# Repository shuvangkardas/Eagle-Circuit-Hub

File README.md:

# Eagle Circuit Hub

<!-- Badges -->
[![GitHub release][release-shield]][release-url]
[![GitHub commits][commits-shield]][commits-url]
[![MIT License][license-shield]][license-url]

## Commonly used Schematic for building circuit board

This is a collection of my schematic for developing designing PCB board in Eagle PCB in a short time. The library contains follwing sub-directory. 
- Microcontroller 
- Power Supply 
- RF
- RF SOC
- Timer
- Sensor
- Switch 
- Connectors
- Memory

### Microcontroller
- ATmega328P.sch
- ATmega328P_SMD_0603.sch
- MSP430FR2433_SMD_0603.sch

### Power Supply 
- LM2596.sch
- LM2596_SMD_0603.sch
- 1117_3.3V.sch
- 1117_3.3V_SMD_0603.sch
- 1117_Adj.sch
- 1117_Adj_SMD_0603.sch
- 7805.sch
- 7805_SMD_0603.sch
- LM2596.sch
- LM2596_SMD_0603.sch
- TPS6273x.sch

## Common SMD Components used
1. Resistor - R-US_R0603
2. Capacitor - C-EUC0603
3. Inductor - L-USL0603 

<!-- MARKDOWN LINKS & IMAGES -->
[release-shield]: https://img.shields.io/github/v/release/shuvangkar/Eagle-Circuit-Hub
[release-url]: https://img.shields.io/github/v/release/shuvangkar/Eagle-Circuit-Hub

[commits-shield]: https://img.shields.io/github/commits-since/shuvangkar/Eagle-Circuit-Hub/v0.1.0
[commits-url]: https://github.com/shuvangkar/Eagle-Circuit-Hub/commits/master

[license-shield]: https://img.shields.io/github/license/shuvangkar/Eagle-Circuit-Hub
[license-url]: https://github.com/shuvangkar/Eagle-Circuit-Hub/blob/master/LICENSE.txt

[linkedin-shield]: https://img.shields.io/badge/-LinkedIn-black.svg?logo=linkedin&colorB=555
[linkedin-url]: https://linkedin.com/in/shuvangkar

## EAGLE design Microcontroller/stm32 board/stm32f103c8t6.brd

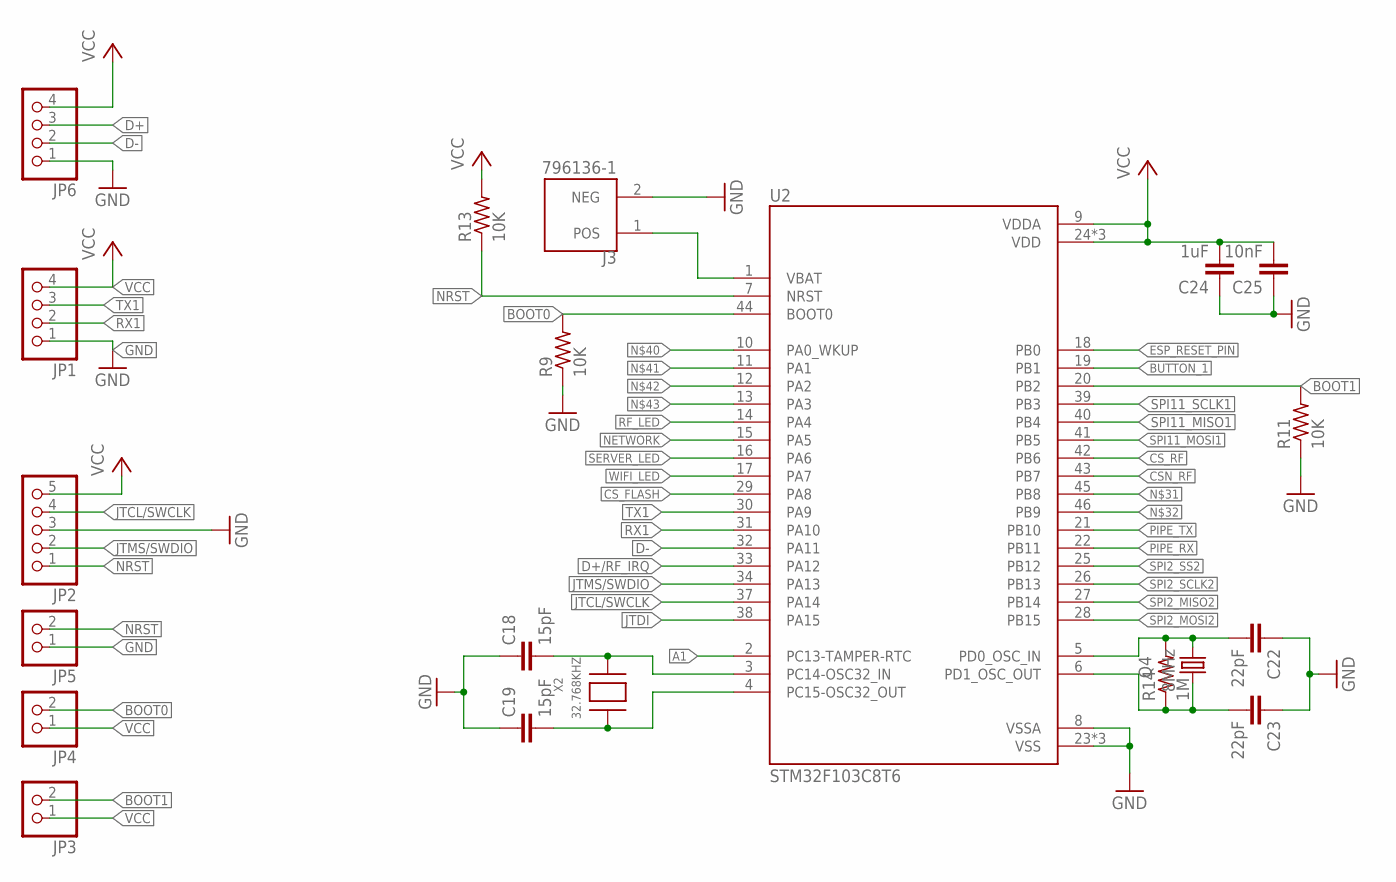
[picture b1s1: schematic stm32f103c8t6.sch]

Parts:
C18, C19: 15pF; C0603
C22, C23: 22pF; C0603
C24: 1uF; C0603
C25: 10nF; C0603
J3: 796136-1; TE_796136-1
JP1, JP6: PINHD-1X4; 1X04
JP2: PINHD-1X5; 1X05
JP3, JP4, JP5: PINHD-1X2; 1X02
Q4: 8MHz; 3.2X2.5_KX-7
R9, R11, R13: 10K; R0603
R14: 1M; R0603
U2: STM32F103C8T6; QFP50P900X900X160-48N
X2: 32.768KHZ; XTAL3215

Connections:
A1: U2.2 (PC13-TAMPER-RTC)
BOOT0: JP4.2, R9.2, U2.44 (BOOT0)
BOOT1: JP3.2, R11.2, U2.20 (PB2)
BUTTON_1: U2.19 (PB1)
CSN_RF: U2.43 (PB7)
CS_FLASH: U2.29 (PA8)
CS_RF: U2.42 (PB6)
D+: JP6.3
D+/RF_IRQ: U2.33 (PA12)
D-: JP6.2, U2.32 (PA11)
ESP_RESET_PIN: U2.18 (PB0)
GND: C18.1, C19.1, C22.1, C23.1, C24.1, C25.1, J3.2 (NEG), JP1.1, JP2.3, JP5.1, JP6.1, R9.1, R11.1, U2.8 (VSSA), U2.23 (VSS), U2.35 (VSS), U2.47 (VSS)
JTCL/SWCLK: JP2.4, U2.37 (PA14)
JTDI: U2.38 (PA15)
JTMS/SWDIO: JP2.2, U2.34 (PA13)
unnamed: C18.2, U2.3 (PC14-OSC32_IN), X2.P$2
unnamed: C19.2, U2.4 (PC15-OSC32_OUT), X2.P$1
unnamed: C23.2, Q4.3 (2), R14.1, U2.6 (PD1_OSC_OUT)
unnamed: C22.2, Q4.1, R14.2, U2.5 (PD0_OSC_IN), U2.45 (PB8)
unnamed: J3.1 (POS), U2.1 (VBAT), U2.46 (PB9)
NETWORK: U2.15 (PA5)
NRST: JP2.1, JP5.2, R13.1, U2.7 (NRST)
PIPE_RX: U2.22 (PB11)
PIPE_TX: U2.21 (PB10)
RF_LED: U2.14 (PA4)
RX1: JP1.2, U2.31 (PA10)
SERVER_LED: U2.16 (PA6)
SPI2_MISO2: U2.27 (PB14)
SPI2_MOSI2: U2.28 (PB15)
SPI2_SCLK2: U2.26 (PB13)
SPI2_SS2: U2.25 (PB12)
SPI11_MISO1: U2.40 (PB4)
SPI11_MOSI1: U2.41 (PB5)
SPI11_SCLK1: U2.39 (PB3)
TX1: JP1.3, U2.30 (PA9)
VCC: C24.2, C25.2, JP1.4, JP2.5, JP3.1, JP4.1, JP6.4, R13.2, U2.9 (VDDA), U2.24 (VDD), U2.36 (VDD), U2.48 (VDD)
WIFI_LED: U2.17 (PA7)

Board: 2 copper layers, 20 parts (0 on the bottom side), 15 nets, no tracks yet.

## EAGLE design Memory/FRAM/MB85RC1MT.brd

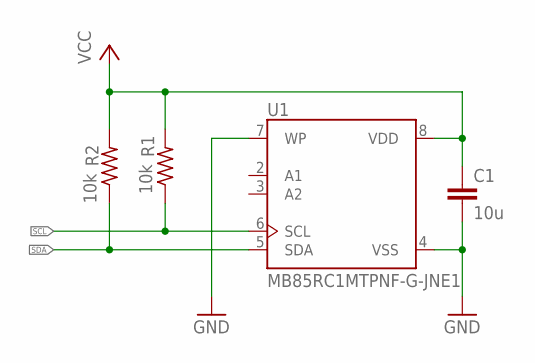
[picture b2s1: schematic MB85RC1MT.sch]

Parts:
C1: 10u; C0603
R1, R2: 10k; R0603
U1: MB85RC1MTPNF-G-JNE1; SOIC127P620X175-8N

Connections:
GND: C1.2, U1.4 (VSS), U1.7 (WP)
SCL: R1.1, U1.6 (SCL)
SDA: R2.1, U1.5 (SDA)
VCC: C1.1, R1.2, R2.2, U1.8 (VDD)

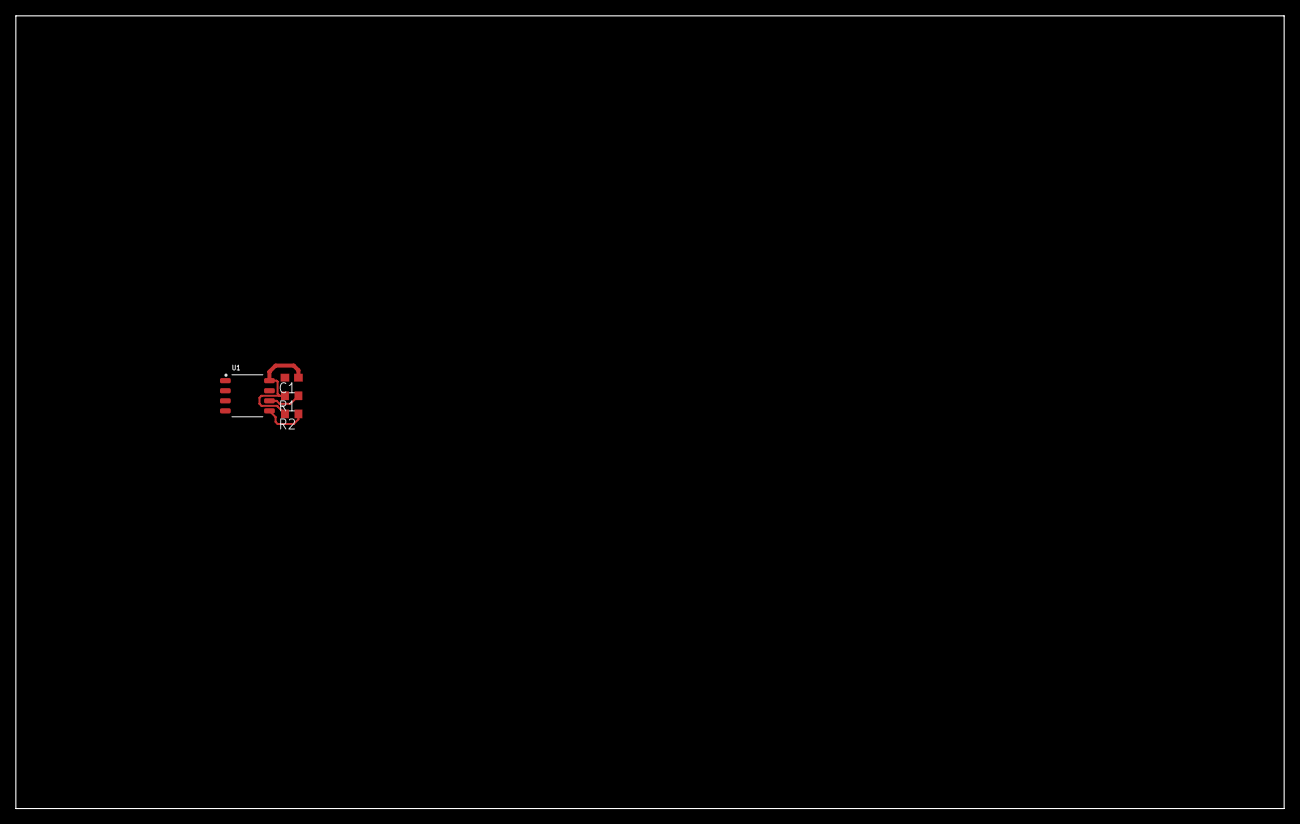
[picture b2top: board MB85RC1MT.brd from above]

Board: 2 copper layers, 160.0 x 100.0 mm, 4 parts (0 on the bottom side), 4 nets.

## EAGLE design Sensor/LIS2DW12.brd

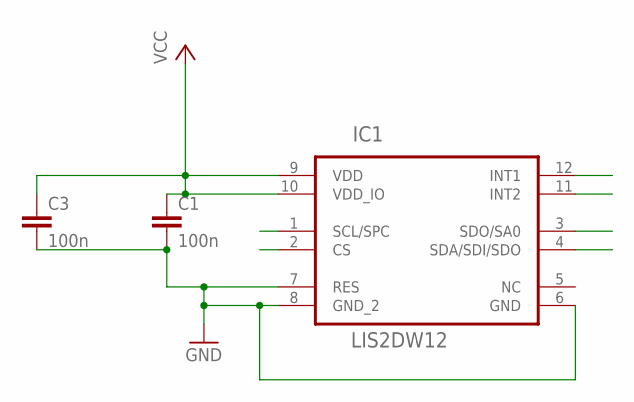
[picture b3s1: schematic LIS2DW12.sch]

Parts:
C1, C3: 100n; C0402
IC1: LIS2DW12; LGA-12

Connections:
GND: C1.2, C3.2, IC1.6 (GND), IC1.7 (RES), IC1.8 (GND_2)
VCC: C1.1, C3.1, IC1.9 (VDD), IC1.10 (VDD_IO)

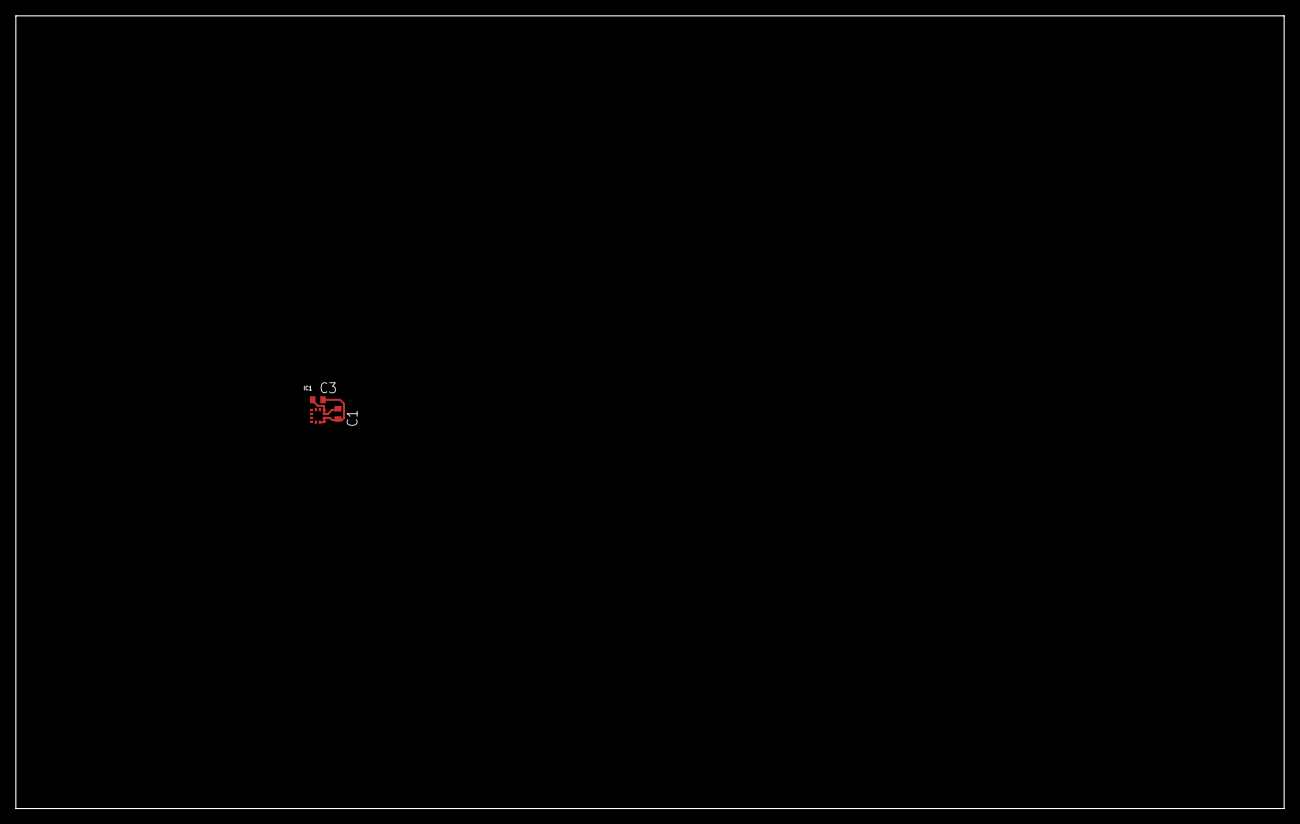
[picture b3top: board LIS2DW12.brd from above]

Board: 2 copper layers, 160.0 x 100.0 mm, 3 parts (0 on the bottom side), 2 nets.

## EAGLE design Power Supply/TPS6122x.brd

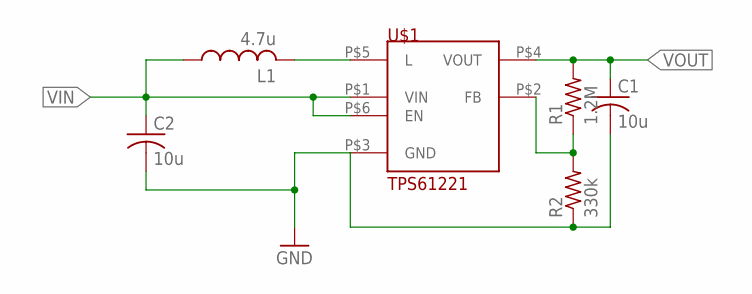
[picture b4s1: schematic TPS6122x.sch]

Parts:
C1, C2: 10u; C3216
L1: 4.7u; L1210
R1: 1.2M; R0603
R2: 330k; R0603
U$1: TPS61221

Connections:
GND: C1.2, C2.2, R2.1, U$1.P$3 (GND)
unnamed: L1.2, U$1.P$5 (L)
unnamed: R1.1, R2.2, U$1.P$2 (FB)
VIN: C2.1, L1.1, U$1.P$1 (VIN), U$1.P$6 (EN)
VOUT: C1.1, R1.2, U$1.P$4 (VOUT)

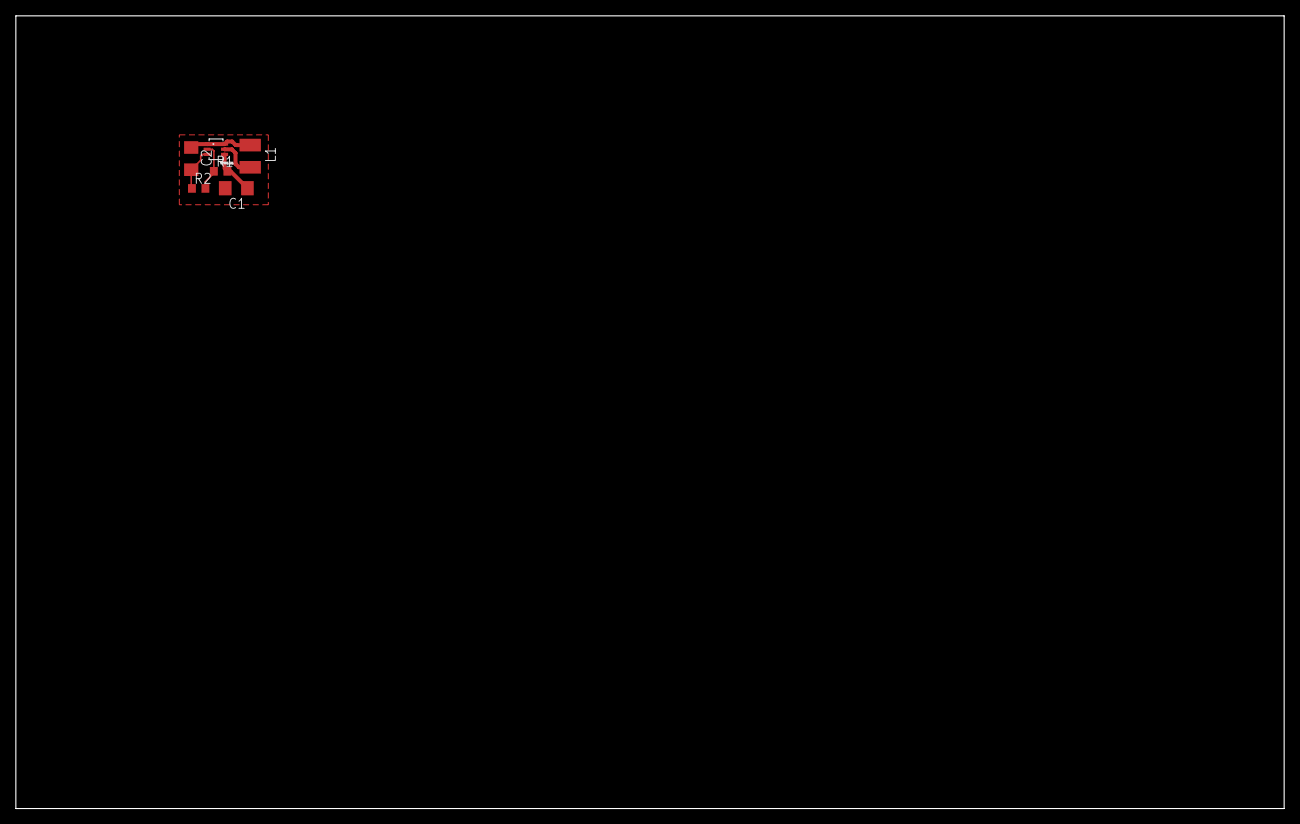
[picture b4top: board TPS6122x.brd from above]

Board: 2 copper layers, 160.0 x 100.0 mm, 6 parts (0 on the bottom side), 5 nets.

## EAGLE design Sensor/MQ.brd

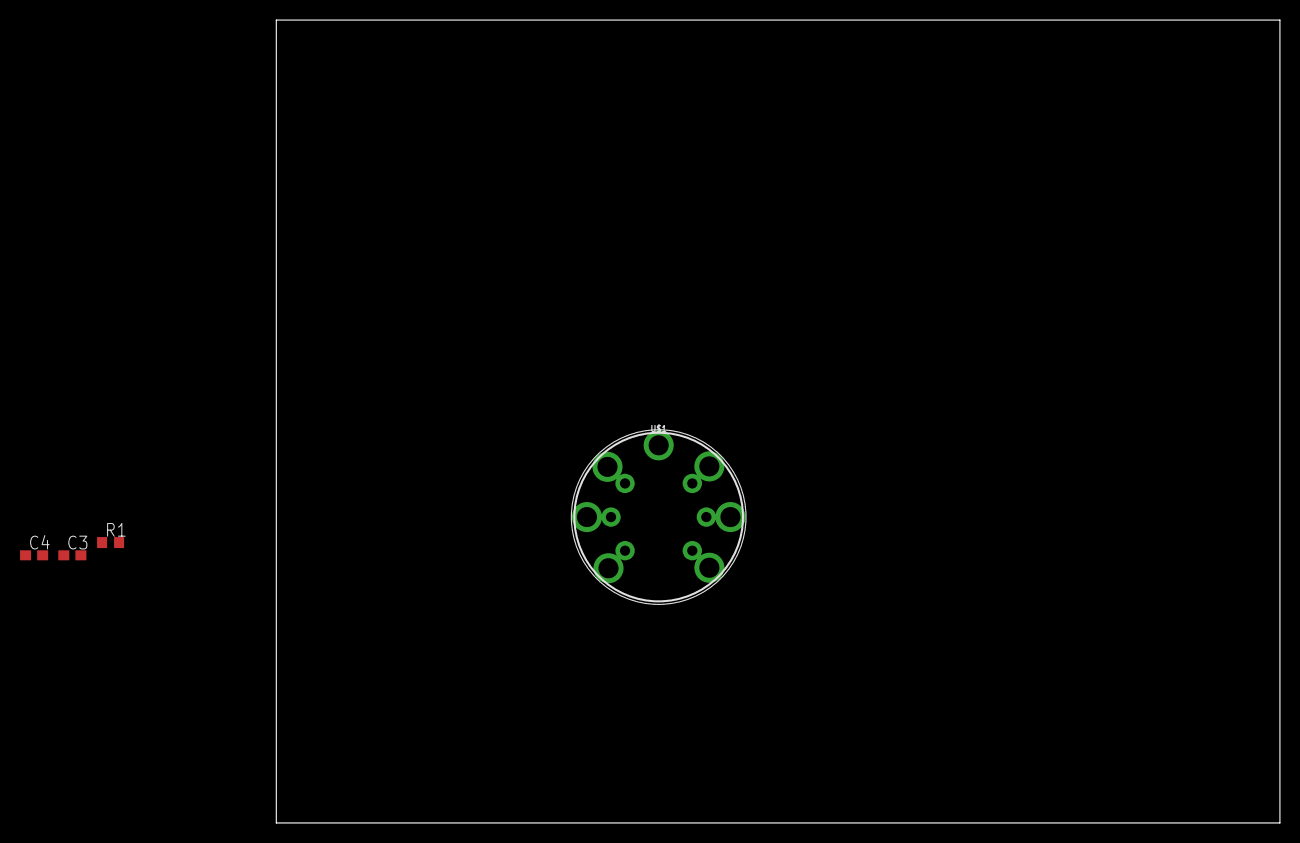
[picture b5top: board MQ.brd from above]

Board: 2 copper layers, 100.0 x 80.0 mm, 4 parts (0 on the bottom side), 3 nets, no tracks yet.

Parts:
C3, C4: C0603
R1: 10k; R0603
U$1: MQ_GAS_SENSOR_SOCKET; GAS_SENSOR_SOCKET

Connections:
GND: C3.2, C4.2, R1.1, U$1.H2, U$1.H22
MQ_OUT: R1.2, U$1.B1, U$1.B2, U$1.B11, U$1.B22
VCC: C3.1, C4.1, U$1.A1, U$1.A2, U$1.A11, U$1.A22, U$1.H1, U$1.H11

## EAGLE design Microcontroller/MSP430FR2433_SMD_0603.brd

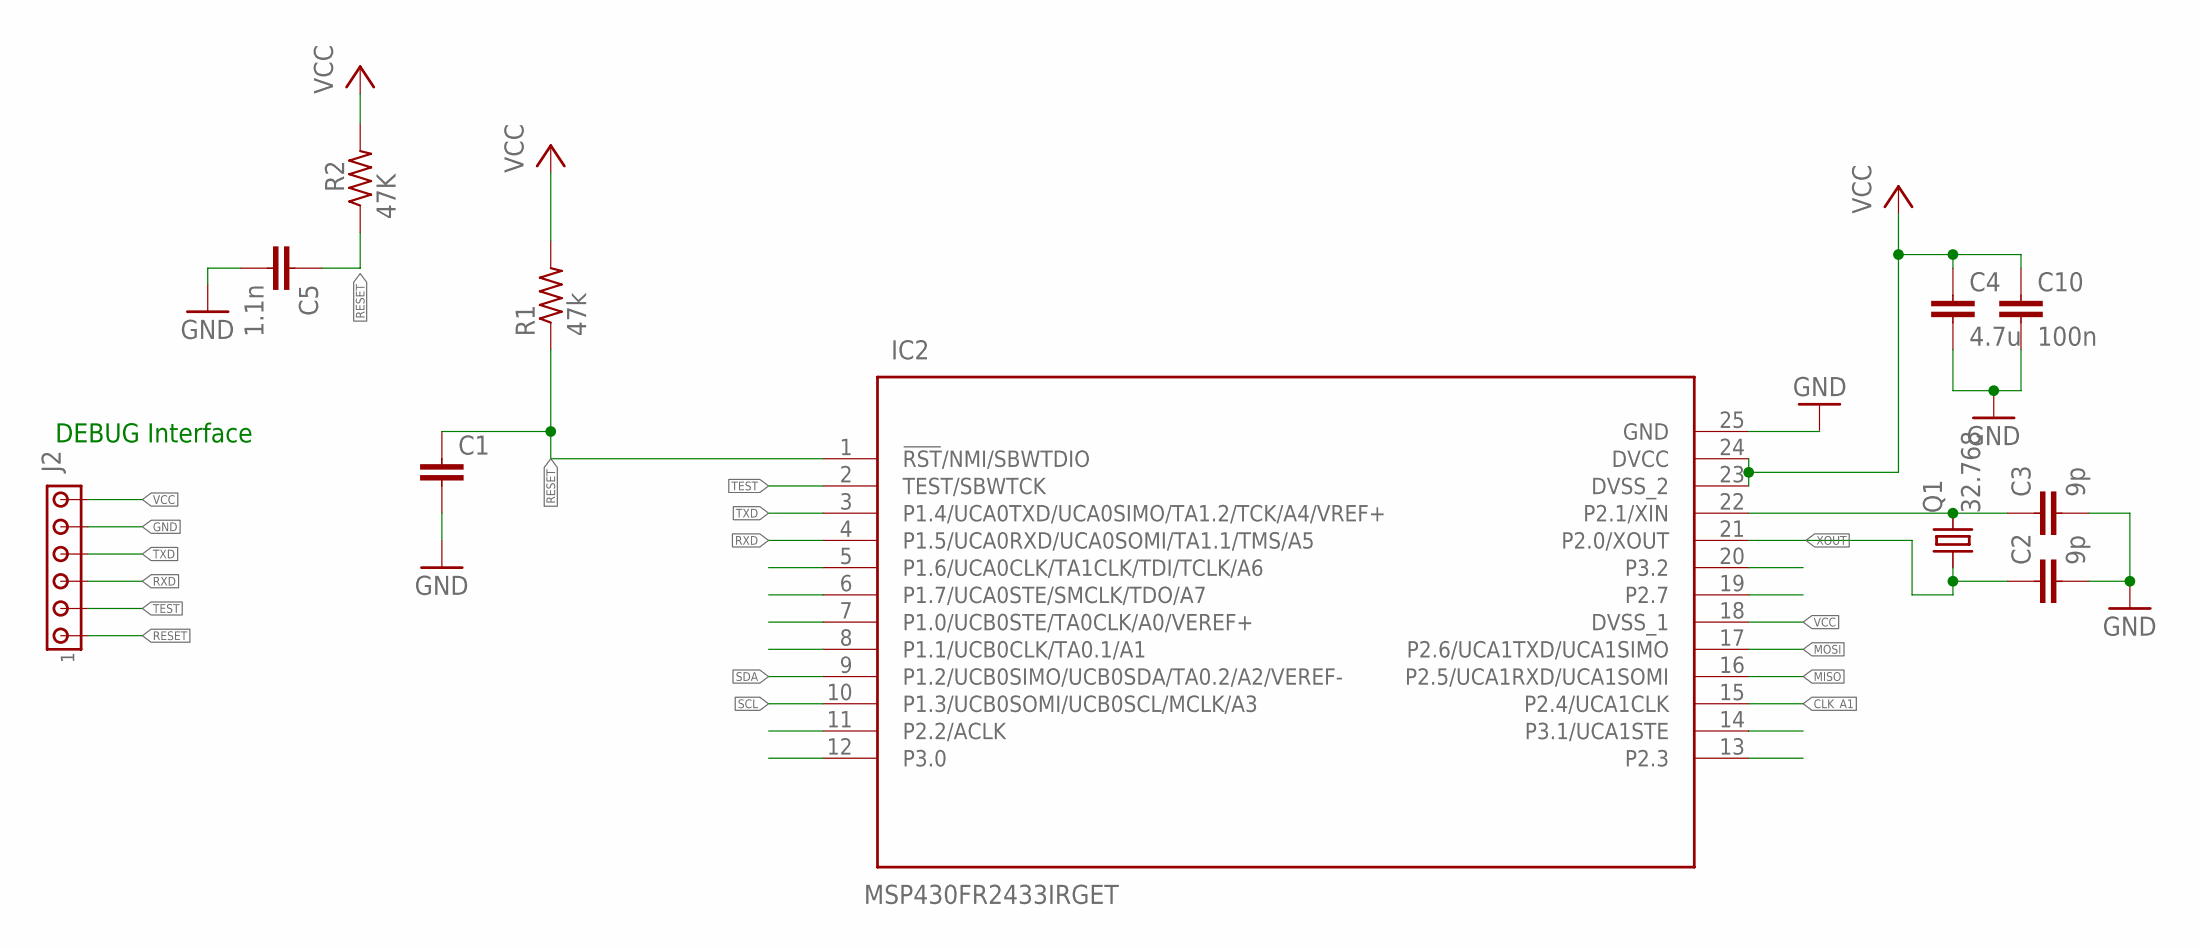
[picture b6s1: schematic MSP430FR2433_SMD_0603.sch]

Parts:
C1: C-EUC0402; C0402
C2, C3: 9p; C0402
C4: 4.7u; C0402
C5: 1.1n; C0402
C10: 100n; C0402
IC2: MSP430FR2433IRGET; QFN50P400X400X100-25N
J2: MTA06-100; 10X06MTA
Q1: 32.768; TC26H
R1: 47k; R0402
R2: 47K; R0402

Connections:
CLK_A1: IC2.15 (P2.4/UCA1CLK)
GND: C1.2, C2.2, C3.2, C4.2, C5.2, C10.2, IC2.25 (GND), J2.5
MISO: IC2.16 (P2.5/UCA1RXD/UCA1SOMI)
MOSI: IC2.17 (P2.6/UCA1TXD/UCA1SIMO)
unnamed: C3.1, IC2.22 (P2.1/XIN), Q1.2
RESET: C1.1, C5.1, IC2.1 (!RST!/NMI/SBWTDIO), J2.1, R1.1, R2.1
RXD: IC2.4 (P1.5/UCA0RXD/UCA0SOMI/TA1.1/TMS/A5), J2.3
SCL: IC2.10 (P1.3/UCB0SOMI/UCB0SCL/MCLK/A3)
SDA: IC2.9 (P1.2/UCB0SIMO/UCB0SDA/TA0.2/A2/VEREF-)
TEST: IC2.2 (TEST/SBWTCK), J2.2
TXD: IC2.3 (P1.4/UCA0TXD/UCA0SIMO/TA1.2/TCK/A4/VREF+), J2.4
VCC: C4.1, C10.1, IC2.18 (DVSS_1), IC2.23 (DVSS_2), IC2.24 (DVCC), J2.6, R1.2, R2.2
XOUT: C2.1, IC2.21 (P2.0/XOUT), Q1.1

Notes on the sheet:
DEBUG Interface

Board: 2 copper layers, 11 parts (0 on the bottom side), 8 nets, no tracks yet.

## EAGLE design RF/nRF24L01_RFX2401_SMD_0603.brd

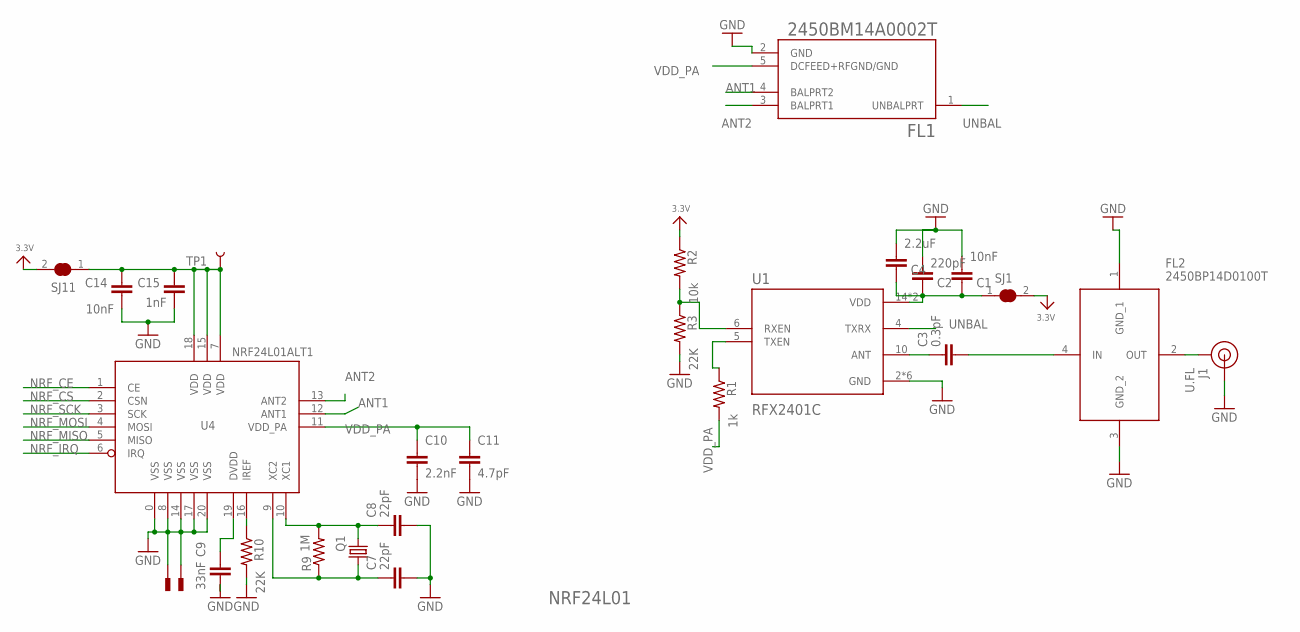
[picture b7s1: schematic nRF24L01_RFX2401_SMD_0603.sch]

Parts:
C1, C14: 10nF; C0603
C2: 220pF; C0603
C3: 0.3pF; C0603
C4: 2.2uF; C0603
C7, C8: 22pF; C0603
C9: 33nF; C0603
C10: 2.2nF; C0603
C11: 4.7pF; C0603
C15: 1nF; C0603
FL1: 2450BM14A0002T; FIL_2450BM14A0002T
FL2: 2450BP14D0100T
J1: U.FL
Q1: KX-7; 3.2X2.5_KX-7
R1: 1k; R0603
R2: 10k; R0603
R3, R10: 22K; R0603
R9: 1M; R0603
SJ1, SJ11: SOLDERJUMPER_CLOSED; SOLDERJUMPER_CLOSEDWIRE
TP1: TEST-POINT3X5; PAD.03X.05
U1: RFX2401C; QFN50P300X300X60-17N
U4: NRF24L01ALT1; QFN20_ALT1
U$27, U$28: PAD; PAD-0.008

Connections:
3.3V: R2.1, SJ1.2, SJ11.2
ANT1: FL1.4 (BALPRT2), U4.12 (ANT1)
ANT2: FL1.3 (BALPRT1), U4.13 (ANT2)
GND: C1.1, C2.1, C4.1, C7.2, C8.2, C9.2, C10.2, C11.2, C14.1, C15.1, FL1.2 (GND), FL2.1 (GND_1), FL2.3 (GND_2), J1.FEED (SIGNAL), R3.2, R10.2, U1.2 (GND), U1.3 (GND), U1.8 (GND), U1.9 (GND), U1.11 (GND), U1.17 (GND), U4.0 (VSS), U4.8 (VSS), U4.14 (VSS), U4.17 (VSS), U4.20 (VSS), U$27.P$1, U$28.P$1
unnamed: C14.2, C15.2, SJ11.1, TP1.P$1, U4.7 (VDD), U4.15 (VDD), U4.18 (VDD)
unnamed: C3.2, FL2.4 (IN)
unnamed: C7.1, Q1.1, R9.1, U4.9 (XC2)
unnamed: FL2.2 (OUT), J1.1 (GND), J1.2 (GND)
unnamed: C3.1, U1.10 (ANT)
unnamed: C1.2, C2.2, C4.2, SJ1.1, U1.14 (VDD), U1.16 (VDD)
unnamed: R1.1, U1.5 (TXEN)
unnamed: C8.1, Q1.3 (2), R9.2, U4.10 (XC1)
unnamed: R2.2, R3.1, U1.6 (RXEN)
unnamed: R10.1, U4.16 (IREF)
unnamed: C9.1, U4.19 (DVDD)
NRF_CE: U4.1 (CE)
NRF_CS: U4.2 (CSN)
NRF_IRQ: U4.6 (IRQ)
NRF_MISO: U4.5 (MISO)
NRF_MOSI: U4.4 (MOSI)
NRF_SCK: U4.3 (SCK)
UNBAL: FL1.1 (UNBALPRT), U1.4 (TXRX)
VDD_PA: C10.1, C11.1, FL1.5 (DCFEED+RFGND/GND), R1.2, U4.11 (VDD_PA)

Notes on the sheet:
NRF24L01

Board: 2 copper layers, 27 parts (0 on the bottom side), 17 nets, no tracks yet.

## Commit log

2020-11-27 Eagle Schematic Library
2020-11-28 gitignore added
2020-11-28 few circuits added
2020-11-28 atmega328 added
2020-11-29 rf, sim , buck circuit added
2020-11-29 flash chip added
2020-11-29 atmega schematic updated
2020-11-29 vcc updated in the circuit
2020-11-29 3.3V regulator added
2020-11-29 led button ckt added
2020-12-01 few ckt updated
2020-12-04 esp12e schematic added
2020-12-07 Rename ATMEGA328PUTQFP_SMD_0603.sch to Microcontroller/ATMEGA328PUTQFP_SMD_0603.sch
2020-12-07 updated atmega ckt
2020-12-07 rtc smd updated
2020-12-07 folder moved
2020-12-07 insig
2020-12-07 nrf raw ckt added
2020-12-07 nrf ic lib modified
2020-12-07 esp8266 updated
2020-12-08 sht21 temp and hum sensor added
2020-12-08 sht21 cap package changed
2020-12-09 mq sensor added
2020-12-13 addesd new components
2020-12-13 esp01 changed
2020-12-13 folder reodered
2020-12-13 TPS supply added
2020-12-13 msp430fr2433 decice symbol updated
2020-12-14 deleted example ckt
2020-12-14 readme updated
2020-12-14 readme update of component list
2020-12-14 License added
2020-12-14 readme badge added
2020-12-14 release updated
2020-12-17 msp430fr2433 updated
2020-12-17 mq updated
2020-12-17 si7051 temp sensor updated
2020-12-17 msp430fr2433 added
2020-12-17 masp430fr2433 modified
2020-12-17 forder reordered and mx flash refactored
2020-12-17 msp430fr2433 basic circuit complete
2020-12-17 lis3dh 402 added
2020-12-17 accelerometer updated
2020-12-17 TPS62745 added
2020-12-17 updated lot of ckt
2020-12-17 tps6122x added
2020-12-20 tmp37 temp sensor added
2020-12-20 TMP117 Temperature sensor added
2020-12-20 hall sensor added
2020-12-21 lis2d12 added
2020-12-21 AA battery holder SMD added in connector folder
2020-12-22 W25N01GV is added
2020-12-22 1gb flash updated
2020-12-22 sensor folder updated
2020-12-22 FRAM PCB added
2020-12-22 folder reordered
2020-12-24 analog amplifier ckt added
2020-12-27 stm32f103c8t6 added
2021-11-10 added new stm board
2021-12-03 readme update

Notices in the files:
parts and their libraries:
crystal-geyer_V1_0: Copyright: Geyer-Electronic
SparkFun-Connectors: Licensing: Creative Commons ShareAlike 4.0 International - https://creativecommons.org/licenses/by-sa/4.0
